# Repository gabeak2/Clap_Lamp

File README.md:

# Clap_Lamp
A lamp that turns on when you clap twice, with a specific timing.  Works pretty well!  I put some in 3d printed lithophane cases and gifted them

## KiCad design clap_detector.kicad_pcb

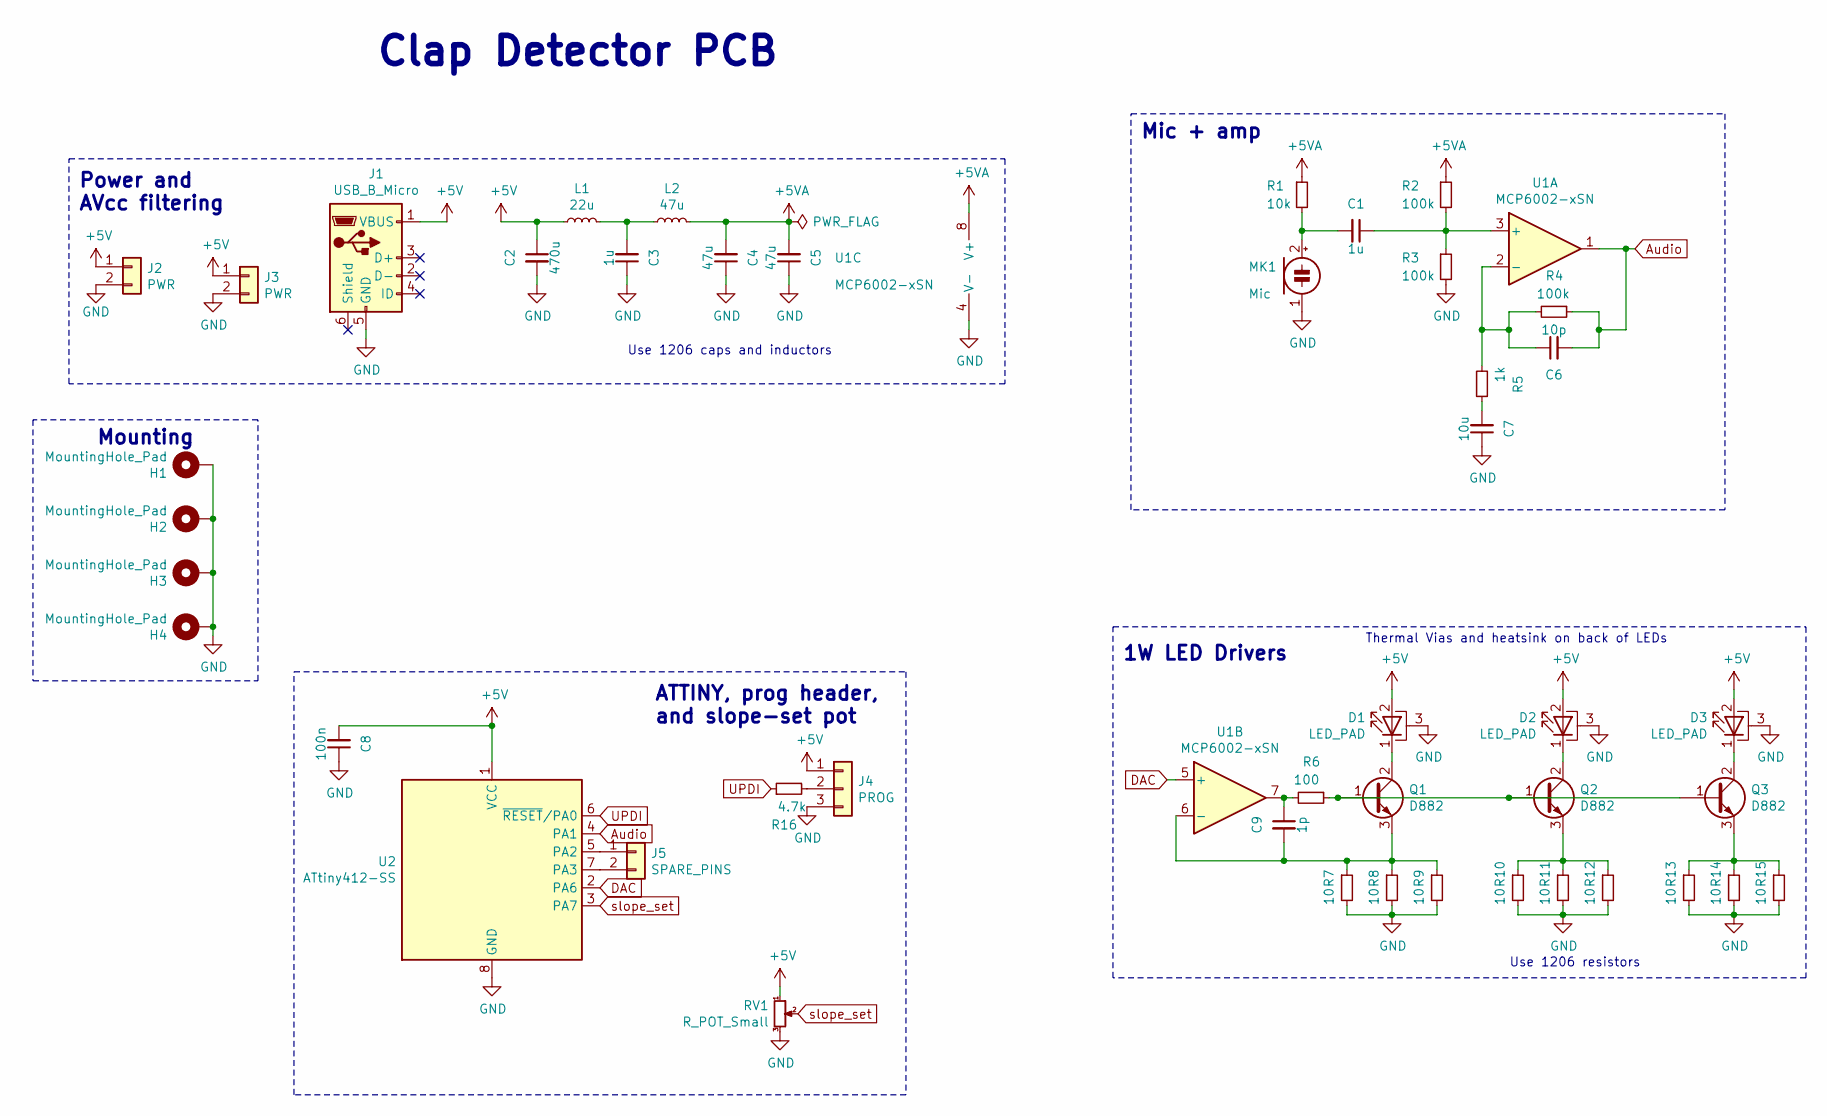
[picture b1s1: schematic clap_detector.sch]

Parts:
C1, C3: 1u; C_0805_2012Metric
C2: 470u; CP_Radial_D13.0mm_P5.00mm
C4, C5: 47u; C_1206_3216Metric
C6: 10p; C_0805_2012Metric
C7: 10u; C_0805_2012Metric
C8: 100n; C_0805_2012Metric
C9: 1p; C_0805_2012Metric
D1, D2, D3: LED_PAD; LED_1W_3W_R8
H1, H2, H3, H4: MountingHole_Pad; MountingHole_3.2mm_M3_Pad_Via
J1: USB_B_Micro; USB_Micro-B_Molex-105017-0001
J2, J3: PWR; PinSocket_1x02_P2.54mm_Vertical
J4: PROG; Molex_KK-254_AE-6410-03A_1x03_P2.54mm_Vertical
J5: SPARE_PINS; PinSocket_1x02_P2.54mm_Vertical
L1: 22u; C_0805_2012Metric
L2: 47u; C_0805_2012Metric
MK1: Mic; electret
Q1, Q2, Q3: D882; SOT-89-3
R1: 10k; R_0805_2012Metric
R2, R3, R4: 100k; R_0805_2012Metric
R5: 1k; R_0805_2012Metric
R6: 100; R_0805_2012Metric
R7, R8, R9, R10, R11, R12, R13, R14, R15: 10; R_1206_3216Metric
R16: 4.7k; R_0805_2012Metric
RV1: R_POT_Small; Potentiometer_Bourns_3296W_Vertical
U1: MCP6002-xSN; SOIC-8_3.9x4.9mm_P1.27mm
U2: ATtiny412-SS; SOIC-8_3.9x4.9mm_P1.27mm

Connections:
+5V: C2.1, C8.2, D1.2 (A), D2.2 (A), D3.2 (A), J1.1 (VBUS), J2.1, J3.1, J4.1, L1.1, RV1.1, U2.1 (VCC); also elsewhere on the board
+5VA: C4.2, C5.2, L2.2, R1.1, R2.1, U1.8 (V+)
Audio: C6.2, R4.1, U1.1, U2.4 (PA1)
DAC: U1.5 (+), U2.2 (PA6)
GND: C2.2, C3.1, C4.1, C5.1, C7.1, C8.1, D1.3 (PAD), D2.3 (PAD), D3.3 (PAD), H1.1, H2.1, H3.1, H4.1, J1.5 (GND), J2.2, J3.2, J4.3, MK1.1 (-), R3.2, R7.2, R8.2, R9.2, R10.2, R11.2, R12.2, R13.2, R14.2, R15.2, RV1.3, U1.4 (V-), U2.8 (GND); also elsewhere on the board
unnamed: C1.1, R2.2, R3.1, U1.3 (+)
unnamed: C1.2, MK1.2 (+), R1.2
unnamed: C3.2, L1.2, L2.1
unnamed: C6.1, R4.2, R5.2, U1.2 (-)
unnamed: C7.2, R5.1
unnamed: C9.1, R6.2, U1.7
unnamed: C9.2, Q1.3 (E), R7.1, R8.1, R9.1, U1.6 (-)
unnamed: D1.1 (K), Q1.2 (C)
unnamed: D2.1 (K), Q2.2 (C)
unnamed: D3.1 (K), Q3.2 (C)
unnamed: J4.2, R16.2
unnamed: J5.1, U2.5 (PA2)
unnamed: J5.2, U2.7 (PA3)
unnamed: Q1.1 (B), Q2.1 (B), Q3.1 (B), R6.1
unnamed: Q2.3 (E), R10.1, R11.1, R12.1
unnamed: Q3.3 (E), R13.1, R14.1, R15.1
UPDI: R16.1, U2.6 (~RESET~/PA0)
slope_set: RV1.2, U2.3 (PA7); also elsewhere on the board

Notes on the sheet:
Use 1206 caps and inductors
Use 1206 resistors
Thermal Vias and heatsink on back of LEDs
1W LED Drivers
Mic + amp
Power and AVcc filtering
ATTINY, prog header, and slope-set pot
Clap Detector PCB
Mounting

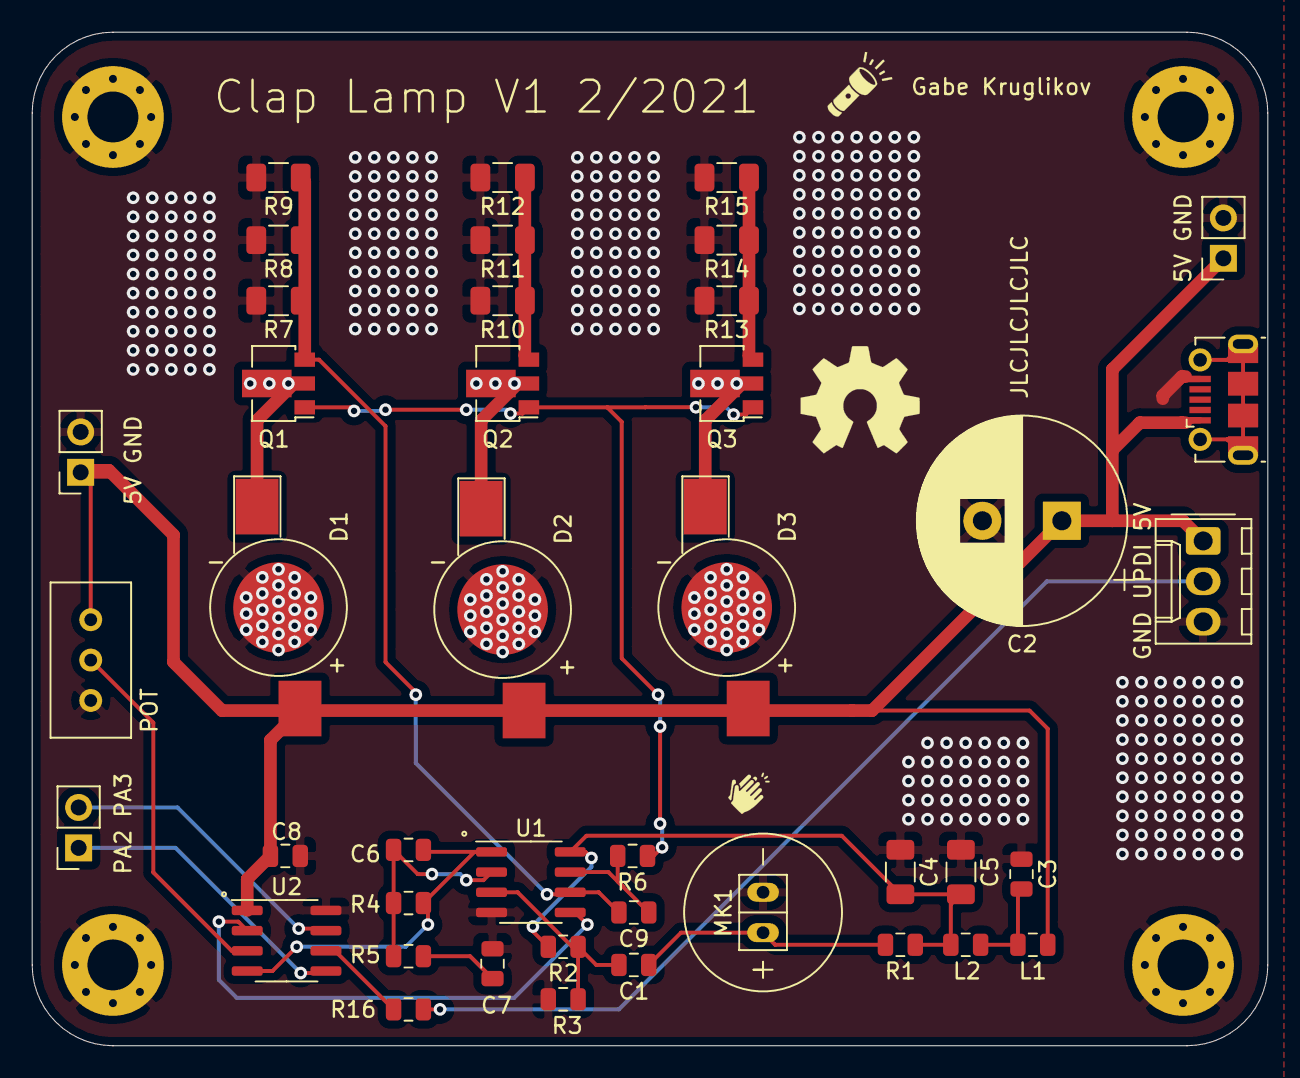
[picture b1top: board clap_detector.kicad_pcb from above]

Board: 2 copper layers, 77.7 x 63.8 mm, 46 parts (0 on the bottom side), 23 nets.

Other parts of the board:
POT: R_POT_Small; Potentiometer_Bourns_3296W_Vertical

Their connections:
+5V: POT.1; also elsewhere on the board
GND: POT.3; also elsewhere on the board
slope_set: POT.2; also elsewhere on the board

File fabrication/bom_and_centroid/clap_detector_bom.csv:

Comment,Designator,Footprint,LCSC part Number
4.7k,R16,R_0805_2012Metric,C17673
MCP6002-xSN,U1,SOIC-8_3.9x4.9mm_P1.27mm,C7377
10,"R15,R14,R13,R12,R11,R10,R9,R8,R7",R_1206_3216Metric,C17903
100,R6,R_0805_2012Metric,C17408
1k,R5,R_0805_2012Metric,C17513
100k,"R4,R3,R2",R_0805_2012Metric,C17407
10k,R1,R_0805_2012Metric,C17414
D882,"Q3,Q2,Q1",SOT-89-3,C9634
47u,L2,C_0805_2012Metric,C14304
22u,L1,C_0805_2012Metric,C32375
1p,C9,C_0805_2012Metric,C14971
100n,C8,C_0805_2012Metric,C49678
10u,C7,C_0805_2012Metric,C15850
10p,C6,C_0805_2012Metric,C1785
47u,"C5,C4",C_1206_3216Metric,C96123
1u,"C3,C1",C_0805_2012Metric,C28323
